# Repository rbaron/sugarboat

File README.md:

<p align="center" style="background-color: white; padding: 10px">
	
<p>

A digital [hydrometer](https://en.wikipedia.org/wiki/Hydrometer). The main use case is measuring the amount of sugar in liquids during the process of beer and wine making.

# How does it work?
Sugarboat floats on top of the liquid being measured. Because of its shifted center of mass, it will float at an angle. This *tilt angle* (see image below) is larger for denser liquids and smaller for less dense liquids. We can then estimate the density of a solution from this angle.

<p align="center">
	
<p>

As is usual in the beer and wine making processes, we can additionally correlate the estimated density of a solution with the amount of sugar present in it.

The estimated [density](https://en.wikipedia.org/wiki/Relative_density) and [sugar content](https://en.wikipedia.org/wiki/Brix) are exposed - along with the temperature, relative humidity, current battery voltage and more - through [Bluetooth Low Energy (BLE)](https://en.wikipedia.org/wiki/Bluetooth_Low_Energy) services. This repository contains examples of how to read these values under [`clients/`](./clients).

# Tech specs
* [nRF52840](https://www.nordicsemi.com/Products/nRF52840) system-on-a-chip
  * Reads sensors, estimates the sugar content and exposes their values via [Bluetooth Low Energy (BLE)](https://en.wikipedia.org/wiki/Bluetooth_Low_Energy) services
* [SHT30](https://www.mouser.com/datasheet/2/682/Sensirion_Humidity_Sensors_SHT3x_Datasheet_digital-971521.pdf) temperature & humidity sensor
* [MPU6050](https://invensense.tdk.com/products/motion-tracking/6-axis/mpu-6050/) accelerometer + gyroscope estimates the tilt angle
* Li-Ion 18650 battery
  * Battery life of over a year on a single charge
  * Built-in [TP4056](http://www.tp4056.com/d/tp4056.pdf)-based charging circuit
* USB-C for battery charging and programming
  * [UF2 support](https://learn.adafruit.com/adafruit-feather-m0-express-designed-for-circuit-python-circuitpython/uf2-bootloader-details) using a [forked Adafruit_nRF52_Bootloader](https://github.com/rbaron/Adafruit_nRF52_Bootloader) allows for direct programming via the USB-C port. This bootloader needs to be flashed to the blank nRF52 chip once using a J-Link or compatible SWD programmer

# Waterproof enclosure
A [preform PET tube (or "petling")](https://en.wikipedia.org/wiki/Polyethylene_terephthalate#Bottle_processing_equipment) is used to enclose the electronics and provide sugarboat with the buoyancy it needs. The printed circuit board is designed to fit tightly into a tube with the inner diameter of around 33 mm and inner height of 123 mm. The board is slightly wider than 33 mm - some light sanding needs to be done to ensure a nice, snuggly fit. I bought my containers from [this eBay offering](https://www.ebay.com/itm/132379354446).

# Repository organization
| Directory                              | Description                                                                                                                              |
|----------------------------------------|------------------------------------------------------------------------------------------------------------------------------------------|
| [`kicad/`](./kicad)                    | Electronics - schematic, PCB layout, bill of materials and fabrication files                                                             |
| [`code/`](./code)                      | Firmware - a [PlatformIO](https://platformio.org/) project using the Arduino framework                                                     |
| [`clients/web/`](./clients/web)         | A web interface for calibrating, configuring and reading sugarboat's sensors                                                             |
| [`clients/arduino/`](./clients/arduino) | A barebones Arduino sketch showing how to read sugarboat's tilt angle, temperature & battery voltage using a Bluetooth Low Energy client |
| [`clients/esphome/`](./clients/esphome) | An [ESPHome](https://esphome.io/) client that integrates with [Home Assistant](https://www.home-assistant.io/) |

# Web client

This client is a web page that connects to sugarboat using the [Web Bluetooth API](https://developer.mozilla.org/en-US/docs/Web/API/Web_Bluetooth_API). It lets you calibrate, configure and read the sensor values right from your web browser, wirelessly.

The web client's source code is in [`clients/web/`](./clients/web).

# Calibration
TODO.

# Bootloader flashing
To support programming via the built-in USB-C port (via [UF2](https://github.com/microsoft/uf2)), sugarboat requires a bootloader to be flashed to the chip. This is a one-time operation.

I have [forked the Adafruit nRF52 Bootloader](https://github.com/rbaron/Adafruit_nRF52_Bootloader) and added support to sugarboat. To build and flash the bootloader:

```bash
$ git clone git@github.com:rbaron/Adafruit_nRF52_Bootloader.git
$ cd Adafruit_nRF52_Bootloader/
$ make BOARD=sugarboat all
$ make BOARD=sugarboat erase
# Look for the build target that contains the merged bootloader + Nordic's SoftDevice and flash it.
# It will be something like _build/build-sugarboat/sugarboat_bootloader-X.X.X-XXX-XXXXXXXXX_s140_6.1.1.hex:
$ nrfjprog --program _build/build-sugarboat/sugarboat_bootloader-0.4.0-149-g5ffac2e_s140_6.1.1.hex -f nrf52 --reset
```

Note that you will need a SWD programmer to complete this operation. A good choice for hobbyists is a [J-Link EDU Mini](https://www.adafruit.com/product/3571). If you buy one, consider getting it from Adafruit.

# License
[CC BY-NC-ND 4.0](https://creativecommons.org/licenses/by-nc-nd/4.0/).

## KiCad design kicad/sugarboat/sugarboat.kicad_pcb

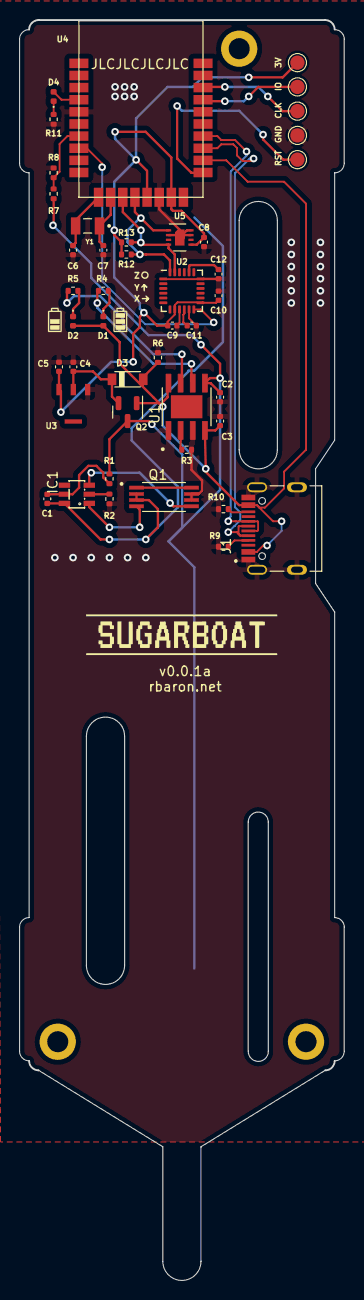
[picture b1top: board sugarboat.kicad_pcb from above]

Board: 2 copper layers, 33.9 x 132.0 mm, 45 parts (1 on the bottom side), 32 nets.

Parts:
BT1: Battery_Cell; BAT_1042_modified
C1, C10, C11: 0.1u; C_0402_1005Metric
C2, C3, C4, C5: 10u; C_0402_1005Metric
C6, C7: 12p; C_0402_1005Metric
C8: 100n; C_0402_1005Metric
C9: 10n; C_0402_1005Metric
C12: 2.2n; C_0402_1005Metric
D1: GREEN; LED_0402_1005Metric
D2, D4: RED; LED_0402_1005Metric
D3: B5819W SL; SOD3716X135N
IC1: DW01A; SOT23-6
J1: TYPE-C-31-M-12; HRO_TYPE-C-31-M-12
Q1: FS8205A; SOP65P640X120-8N
Q2: AO3401A; SOT-23
R1: 100; R_0402_1005Metric
R2, R4, R5, R11: 1k; R_0402_1005Metric
R3: 2k; R_0402_1005Metric
R6, R12, R13: 10k; R_0402_1005Metric
R7, R8: 470k; R_0402_1005Metric
R9, R10: 5.1k; R_0402_1005Metric
TP1, TP2, TP3, TP4, TP5: TestPoint; TestPoint_Pad_D1.5mm
U1: TP4056; SOP127P600X175-9N
U2: MPU-6050; InvenSense_QFN-24_4x4mm_P0.5mm
U3: HT7330; SOT89
U4: E73-2G4M08S1C; E73-2G4M08S1C-modified
U5: SHT30-DIS; Sensirion_DFN-8-1EP_2.5x2.5mm_P0.5mm_EP1.1x1.7mm
Y1: 32.768 kHz; XTAL_NX3215SA-32.768K-STD-MUA-14

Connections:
+3V0: C5.2, C8.2, C9.2, C10.1, R12.2, R13.1, TP5.1, U2.8 (VDDIO), U2.13 (VDD), U3.VOUT, U4.19 (VDD), U4.23 (VDDH), U5.5 (VDD)
+5V: C3.2, D1.2 (A), D2.2 (A), D3.A, J1.A4B9 (VBUS), J1.B4A9 (VBUS), Q2.1 (G), R6.1, U1.4 (VCC), U1.8 (CE), U4.27 (VBUS)
+BATT: BT1.+, C2.2, Q2.3 (D), R1.1, R7.1, U1.5 (BAT)
BATT_SEN: R7.2, R8.1, U4.7 (P0.02/AIN0)
GND: C2.1, C3.1, C4.1, C5.1, C6.1, C7.1, C8.1, C9.1, C10.2, C11.2, C12.1, J1.A1B12 (GND), J1.B1A12 (GND), J1.S1 (SHIELD), J1.S2 (SHIELD), J1.S3 (SHIELD), J1.S4 (SHIELD), Q1.6, Q1.7, R2.2, R3.2, R6.2, R8.2, R9.2, R10.2, R11.2, TP2.1, U1.1 (TEMP), U1.3 (GND), U2.1 (CLKIN), U2.9 (AD0), U2.11 (FSYNC), U2.18 (GND), U3.GND, U4.5 (GND@1), U4.21 (GND@2), U5.2 (ADDR), U5.7 (R), U5.8 (VSS), U5.9 (VSS)
IMU_INT: U2.12 (INT), U4.8 (P0.29/AIN5)
LED: D4.2 (A), U4.4 (P0.28/AIN4)
unnamed: BT1.-, C1.1, IC1.6 (GND), Q1.2, Q1.3
unnamed: C1.2, IC1.5 (VCC), R1.2
unnamed: C4.2, D3.C, Q2.2 (S), U3.VIN
unnamed: C6.2, U4.11 (P0.00/XL1), Y1.2
unnamed: C7.2, U4.13 (P0.01/XL2), Y1.1
unnamed: C11.1, U2.10 (REGOUT)
unnamed: C12.2, U2.20 (CPOUT)
unnamed: D1.1 (K), R4.1
unnamed: D2.1 (K), R5.1
unnamed: D4.1 (K), R11.1
unnamed: IC1.1 (OD), Q1.4
unnamed: IC1.2 (CS), R2.1
unnamed: IC1.3 (OC), Q1.5
unnamed: J1.A5 (CC1), R9.1
unnamed: J1.B5 (CC2), R10.1
unnamed: R3.1, U1.2 (PROG)
unnamed: R4.2, U1.6 (~STDBY)
unnamed: R5.2, U1.7 (~CHRG)
RESET: TP1.1, U4.26 (P0.18/RESET)
SCL: R13.2, U2.23 (SCL), U4.15 (P0.05/AIN3), U5.4 (SCL)
SDA: R12.1, U2.24 (SDA), U4.17 (P1.09), U5.1 (SDA)
SWDCLK: TP3.1, U4.39 (SWDCLK)
SWDIO: TP4.1, U4.37 (SWDIO)
USB D+: J1.A6 (DP1), J1.B6 (DP2), U4.31 (DP)
USB D-: J1.A7 (DN1), J1.B7 (DN2), U4.29 (DM)

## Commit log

2021-12-25 Initial PlatformIO setup for the ItsyBitsy nRF52840
2021-12-25 Reading sensor with adafruit/Adafruit MPU6050@^2.0.5
2021-12-25 Calibration with i2cdevlib works
2021-12-25 Reading Euler angles sort of works, but calibration seems off
2021-12-26 First stab at calculating the angle between the sensor and the z axis
    Sort of works, except if we rotate itaround the y axis. I would love for
    it to be independent of this rotation.
2022-01-02 Initial KiCad project
2022-01-03 First routing
    Sort of works, but can be improved.
2022-01-04 Better routing
2022-01-04 Small fixes in the PCB layout & artwork
2022-01-04 Added LCSC part numbers to all components
2022-01-05 Sent v0.0.0a PCB for fabrication
2022-01-05 Renamed KiCad project to sugarboat
2022-01-08 Renames code to sugarboat. Adds config persistence
2022-01-08 Hacky BLE/Serial logger mesh up
2022-01-09 BLE write callback works
2022-01-11 Adds BLE orientation characteristic
2022-01-12 First successful test with the real v0.0.1a board!!
2022-01-13 Temp & batt voltage sensor + BLE work
2022-01-16 Adds Euler angles to the orientation service
2022-01-16 Adds Brix & specific gravity (SG) estimates to sensor characteristic
2022-01-19 A first stab in low power mode for the MPU6050
    I'm not super happy with it. The MPU is put to sleep and the DMP is
    disabled. When they are turned on, it seems to take ~5 s for the
    orientation to converge.
    Another possibility is to leave it running and lower the sample rate,
    but I have to do some measurements to understand how power hungry and
    efficient that would be.
2022-01-21 Several minor improvements to the firmware
2022-01-21 Adds clients/arduino/central_example
    It's a Arduino-based BLE central that connects to the sugarboat and is
    notified whenever new sensor values are published to the sensor BLE
    characteristic.
2022-01-25 Adds README.md
2022-01-25 Adds clients/esphome/
2022-01-25 Light cleanup
2022-01-25 Code clean up
2022-01-25 Moves web client React project to this repo
2022-01-30 [clients/web] Deploying automation to github pages
2022-01-30 [clients/arduino/esp32] Barebones ESP32 Arduino client
2022-02-06 Updates license to CC BY-NC-ND 4.0
2022-02-23 Implements an alternative, lower power IMU usage pattern
    For normal operation, sugarboat is mostly static, meaning the only
    acceleration is due to gravity. Gyroscope effects should be negligible,
    so we don't need fancy, power-hungy sensor fusion algorithms.
    This commit introduces a quick experiment without using the DMP from the
    MPU5060, and calculating the tilt directly from the accelerations alone.
2022-03-04 A bunch of dirty power-optimization changes
2022-03-05 Clean up mpu6050 code
    Removed all DMP code in favor of much lower power-friendly
    acceleration-only mode. It's a bit noisier, but it's a good tradeoff
    from my tests.
2022-03-05 Removes mentions of orientation characteristic from the web UI
2022-03-05 Uses ArduinoJson for config serialization
2022-03-05 Cleanup
2022-03-05 More cleanup
2022-03-05 Makes the BLE name configurable
2022-03-05 Makes sleeping time configurable
2022-03-06 Implements a BLE reset handler
2022-03-17 Includes MPU's internal temperature in the BLE payload
2022-08-26 Sets TX power to 8
    Average current in connected state increases from 141 uA to 166 uA.
    Worth it.
2023-04-13 Backup & Restore configs. Fast/slow adv and conn intervals
2023-04-13 Slightly less pain inducing string stream hack
2023-04-13 Include guards
2023-04-16 Change kFastConnIntervalSwitchSec to 60 s
